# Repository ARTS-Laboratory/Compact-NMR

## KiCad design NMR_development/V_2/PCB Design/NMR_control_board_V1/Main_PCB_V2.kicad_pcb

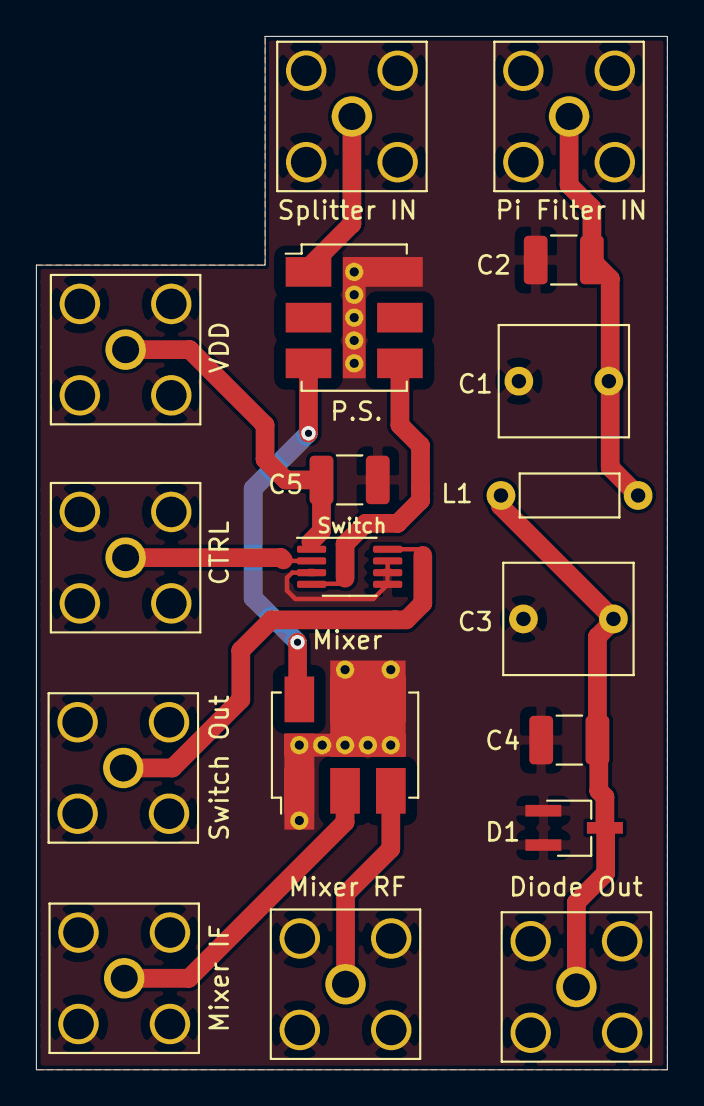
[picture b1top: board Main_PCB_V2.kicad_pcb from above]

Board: 2 copper layers, 35.1 x 57.4 mm, 18 parts (0 on the bottom side), 11 nets.

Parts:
C1, C3: CTRIM; C_Rect_L7.0mm_W6.0mm_P5.00mm
C2, C4, C5: C; C_1210_3225Metric_Pad1.33x2.70mm_HandSolder
CTRL: Conn_Coaxial; SMA_Amphenol_132203-12_Horizontal
D1: D_Schottky_x2_Serial_AKC; TSOT-23_HandSoldering
Diode Out: Conn_Coaxial; SMA_Amphenol_132203-12_Horizontal
L1: INDUCTOR; L_Axial_L5.3mm_D2.2mm_P7.62mm_Horizontal_Vishay_IM-1
Mixer: ADE-6; Mini-Circuits_CD542_LandPatternPL-052
Mixer IF: Conn_Coaxial; SMA_Amphenol_132203-12_Horizontal
Mixer RF: Conn_Coaxial; SMA_Amphenol_132203-12_Horizontal
P.S.: ADP-2-1W; Mini-Circuits_CD636_LandPatternPL-035
Pi Filter IN: Conn_Coaxial; SMA_Amphenol_132203-12_Horizontal
Splitter IN: Conn_Coaxial; SMA_Amphenol_132203-12_Horizontal
Switch: ADG901BRMZ; MSOP-8_3x3mm_P0.65mm
Switch Out: Conn_Coaxial; SMA_Amphenol_132203-12_Horizontal
VDD: Conn_Coaxial; SMA_Amphenol_132203-12_Horizontal

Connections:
GND: C1.2, C2.2, C3.2, C4.2, C5.2, CTRL.2, D1.1, D1.2, Diode Out.2, Mixer.1, Mixer.4, Mixer.5, Mixer IF.2, Mixer RF.2, P.S..6, Pi Filter IN.2, Splitter IN.2, Switch.3, Switch.5, Switch.6, Switch.7, Switch Out.2, VDD.2
unnamed: C1.1, C2.1, L1.1, Pi Filter IN.1
unnamed: C3.1, C4.1, D1.3, Diode Out.1, L1.2
unnamed: C5.1, Switch.1, VDD.1
unnamed: P.S..1, Splitter IN.1
unnamed: CTRL.1, Switch.2
unnamed: Mixer.3, Mixer RF.1
unnamed: Mixer.2, Mixer IF.1
unnamed: Switch.8, Switch Out.1
unnamed: Mixer.6, P.S..3
unnamed: P.S..4, Switch.4

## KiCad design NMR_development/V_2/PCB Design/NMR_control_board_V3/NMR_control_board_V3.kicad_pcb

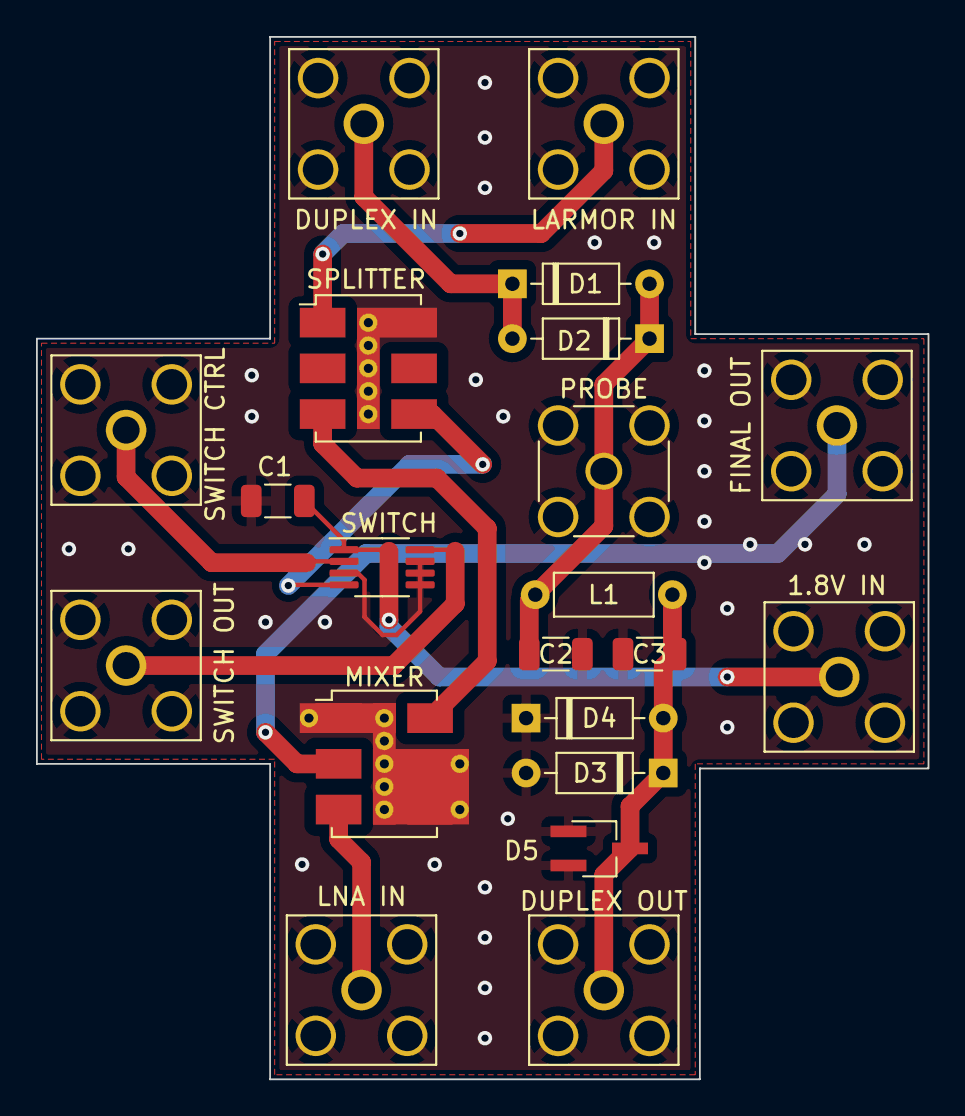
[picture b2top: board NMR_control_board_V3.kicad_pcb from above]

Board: 2 copper layers, 49.5 x 57.9 mm, 21 parts (0 on the bottom side), 12 nets.

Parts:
1.8V IN: Conn_Coaxial; SMA_Amphenol_132203-12_Horizontal
C1: 0.1 uF; C_1206_3216Metric
C2, C3: C; C_1206_3216Metric
D1, D2, D3, D4: 1N4148; D_DO-35_SOD27_P7.62mm_Horizontal
D5: D_Schottky_Dual_Series_AKC; TSOT-23_HandSoldering
DUPLEX IN: Conn_Coaxial; SMA_Amphenol_132203-12_Horizontal
DUPLEX OUT: Conn_Coaxial; SMA_Amphenol_132203-12_Horizontal
FINAL OUT: Conn_Coaxial; SMA_Amphenol_132203-12_Horizontal
L1: INDUCTOR; L_Axial_L5.3mm_D2.2mm_P7.62mm_Horizontal_Vishay_IM-1
LARMOR IN: Conn_Coaxial; SMA_Amphenol_132203-12_Horizontal
LNA IN: Conn_Coaxial; SMA_Amphenol_132203-12_Horizontal
MIXER: ADE-6; Mini-Circuits_CD542_LandPatternPL-052
PROBE: Conn_Coaxial; SMA_Amphenol_132291-12_Vertical
SPLITTER: ADP-2-1W; Mini-Circuits_CD636_LandPatternPL-035
SWITCH: ADG901BRMZ; MSOP-8_3x3mm_P0.65mm
SWITCH CTRL: Conn_Coaxial; SMA_Amphenol_132203-12_Horizontal
SWITCH OUT: Conn_Coaxial; SMA_Amphenol_132203-12_Horizontal

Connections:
GND: 1.8V IN.2 (Ext), C1.1, C2.2, C3.2, D3.2 (A), D4.1 (K), D5.1 (A), D5.2 (K), DUPLEX IN.2 (Ext), DUPLEX OUT.2 (Ext), FINAL OUT.2 (Ext), LARMOR IN.2 (Ext), LNA IN.2 (Ext), MIXER.1 (GND), MIXER.4 (GND), MIXER.5 (GND), PROBE.2 (Ext), SPLITTER.6 (GND), SWITCH.3 (GND), SWITCH.5 (GND), SWITCH.6 (GND), SWITCH.7 (GND), SWITCH CTRL.2 (Ext), SWITCH OUT.2 (Ext)
unnamed: 1.8V IN.1 (In), C1.2, SWITCH.1 (VDD)
unnamed: C2.1, D1.2 (A), D2.1 (K), L1.1, PROBE.1 (In)
unnamed: C3.1, D3.1 (K), D4.2 (A), D5.3 (common), DUPLEX OUT.1 (In), L1.2
unnamed: D1.1 (K), D2.2 (A), DUPLEX IN.1 (In)
unnamed: LARMOR IN.1 (In), SPLITTER.1 (SUM)
unnamed: SWITCH.2 (CTRL), SWITCH CTRL.1 (In)
unnamed: LNA IN.1 (In), MIXER.3 (RF)
unnamed: FINAL OUT.1 (In), MIXER.2 (IF)
unnamed: SWITCH.8 (RF2), SWITCH OUT.1 (In)
unnamed: MIXER.6 (LO), SPLITTER.3 (PORT1)
unnamed: SPLITTER.4 (PORT2), SWITCH.4 (RF1)

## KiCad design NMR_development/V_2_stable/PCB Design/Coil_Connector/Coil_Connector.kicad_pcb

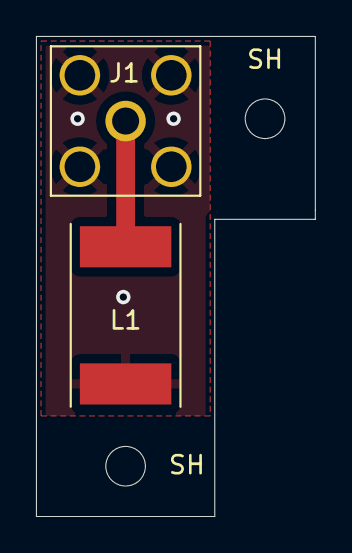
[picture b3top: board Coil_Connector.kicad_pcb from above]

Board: 2 copper layers, 15.5 x 26.7 mm, 4 parts (0 on the bottom side), 2 nets.

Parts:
J1: Conn_Coaxial; SMA_Amphenol_132203-12_Horizontal
L1: L; L_Coil
SH: MountingHole_2.2mm_M2
SH#2: MountingHole_2.2mm_M2

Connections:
GND: J1.2, L1.2
unnamed: J1.1, L1.1

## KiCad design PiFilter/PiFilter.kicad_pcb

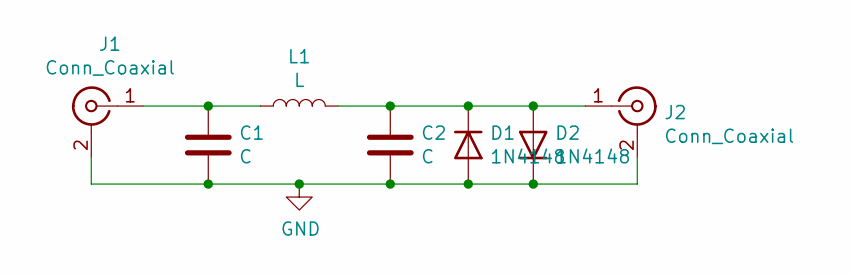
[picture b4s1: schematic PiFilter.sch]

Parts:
C1, C2: C; C_1210_3225Metric_Pad1.33x2.70mm_HandSolder
D1, D2: 1N4148; D_DO-35_SOD27_P7.62mm_Horizontal
J1, J2: Conn_Coaxial; SMA_Amphenol_132203-12_Horizontal
L1: L; L_Axial_L5.3mm_D2.2mm_P7.62mm_Horizontal_Vishay_IM-1

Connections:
GND: C1.2, C2.2, D1.2 (A), D2.1 (K), J1.2 (Ext), J2.2 (Ext)
unnamed: C1.1, J1.1 (In), L1.1
unnamed: C2.1, D1.1 (K), D2.2 (A), J2.1 (In), L1.2

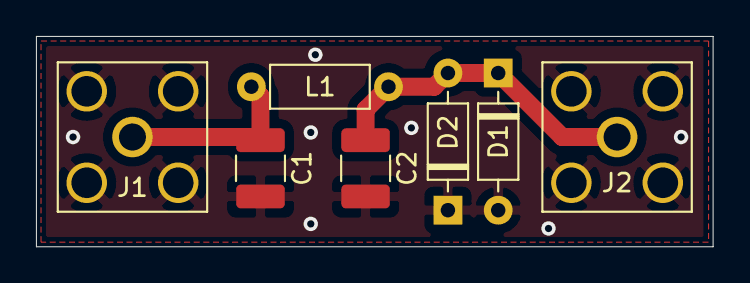
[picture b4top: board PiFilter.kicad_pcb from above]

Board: 2 copper layers, 37.6 x 11.7 mm, 7 parts (0 on the bottom side), 3 nets.

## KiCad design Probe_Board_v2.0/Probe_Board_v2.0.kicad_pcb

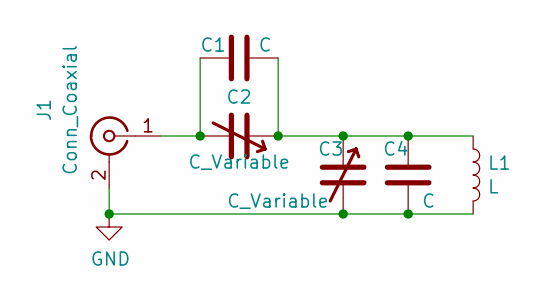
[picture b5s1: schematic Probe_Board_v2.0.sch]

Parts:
C1, C4: C; C_1210_3225Metric_Pad1.33x2.70mm_HandSolder
C2: C_Variable; C_Trim_5501
C3: C_Variable; C_Trim_AP55HV
J1: Conn_Coaxial; SMA_Amphenol_132203-12_Horizontal
L1: L; L_Coil

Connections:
GND: C3.2, C3.3, C4.2, J1.2 (Ext), L1.2
unnamed: C1.1, C2.1, C3.1, C4.1, L1.1
unnamed: C1.2, C2.2, C2.3, J1.1 (In)

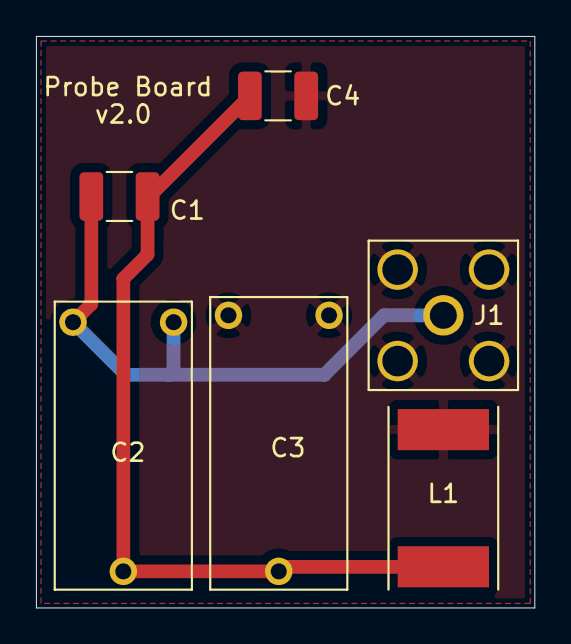
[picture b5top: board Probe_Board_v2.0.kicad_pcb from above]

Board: 2 copper layers, 27.7 x 31.8 mm, 6 parts (0 on the bottom side), 3 nets.
